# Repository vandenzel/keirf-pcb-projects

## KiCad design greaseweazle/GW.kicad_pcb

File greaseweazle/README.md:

# Greaseweazle

This is a fork of [Keir Fraser](https://github.com/keirf)'s design for a very simple Greaseweazle hardware implementation consisting of just one STM32 Blue Pill and four or five pull-up resistors.

This design is upgraded to the KiCAD 6 file naming and formatting scheme (`*.kicad_pro` instead of `*.pro`).

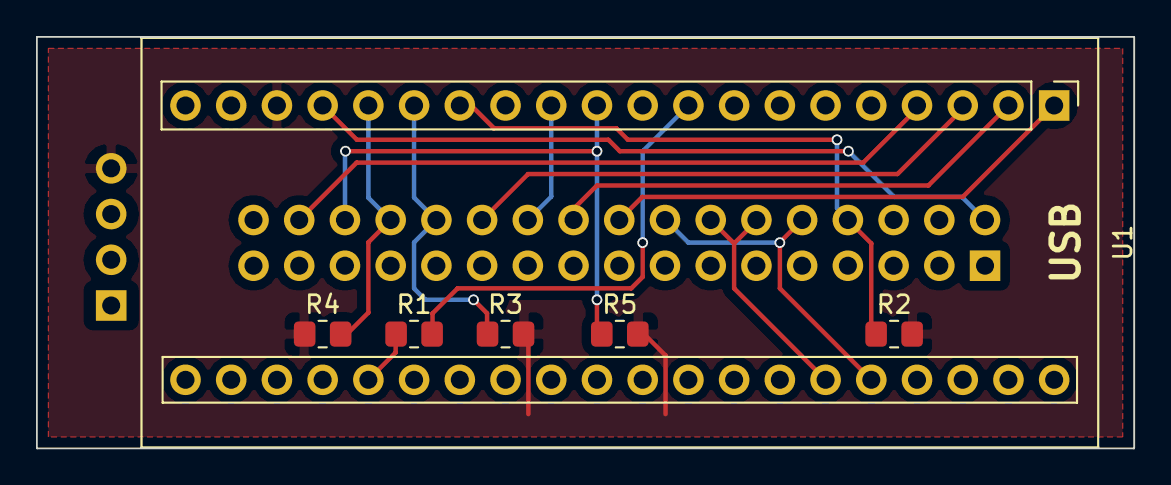
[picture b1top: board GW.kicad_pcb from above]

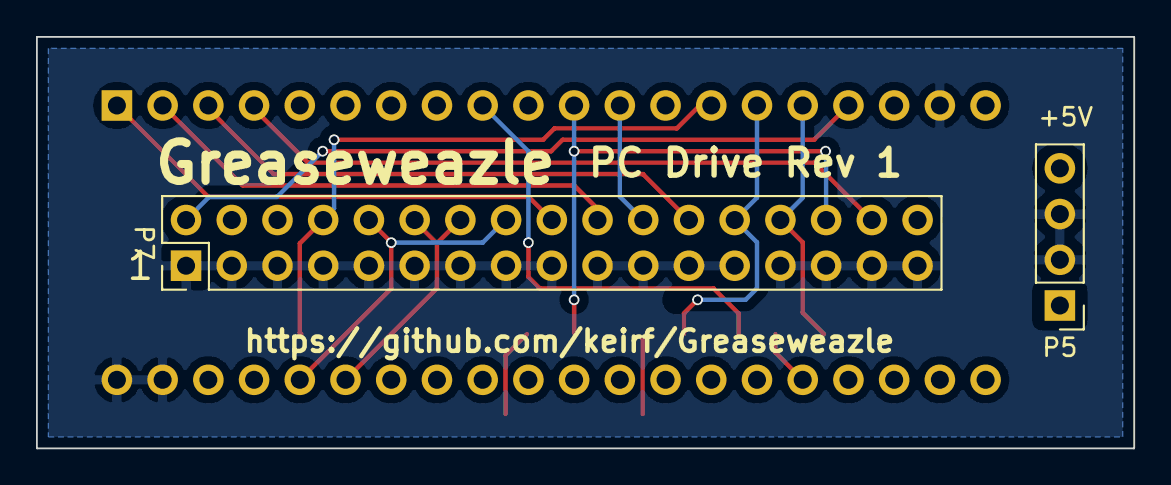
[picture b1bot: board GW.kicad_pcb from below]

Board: 2 copper layers, 61.0 x 22.9 mm, 8 parts (2 on the bottom side), 16 nets.

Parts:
P5: POWER; PinHeader_1x04_P2.54mm_Vertical
P7: FLOPPY; PinHeader_2x17_P2.54mm_Vertical
R1: 1.5K; R_0805_2012Metric_Pad1.20x1.40mm_HandSolder
R2, R3, R4, R5: 1K; R_0805_2012Metric_Pad1.20x1.40mm_HandSolder
U1: YAAJ_BluePill_Part_Like; YAAJ_BluePill_2

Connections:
+5V: P5.4, R2.1, R3.1, R4.1, R5.1, U1.18 (5V)
/USB_CONN: R1.1, U1.25 (PA0)
/USB_DP: R1.2, U1.9 (PA12)
/_DENSEL: P7.2, U1.17 (PB9)
/_DIR: P7.18, U1.1 (PB12)
/_DKRD: P7.30, R5.2, U1.11 (PB3)
/_DKWD: P7.22, U1.12 (PB4)
/_DKWE: P7.24, U1.3 (PB14)
/_INDEX: P7.8, R2.2, U1.14 (PB6)
/_MTR: P7.10, P7.16, U1.36 (PB11)
/_SEL: P7.12, P7.14, U1.35 (PB10)
/_SIDE: P7.32, U1.4 (PB15)
/_STEP: P7.20, U1.2 (PB13)
/_TRK0: P7.26, R3.2, U1.15 (PB7)
/_WRPROT: P7.28, R4.2, U1.16 (PB8)
GND: P5.2, P5.3, P7.1, P7.3, P7.5, P7.7, P7.9, P7.11, P7.13, P7.15, P7.17, P7.19, P7.21, P7.23, P7.25, P7.27, P7.29, P7.31, P7.33, U1.19 (GND), U1.39 (GND), U1.40 (GND)

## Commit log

2022-08-15 Update to KiCAD 6; added 3D model of the BluePill
